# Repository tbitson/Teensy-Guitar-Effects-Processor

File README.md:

Teensy Guitar Effects Processor

This is an in-work project!

The Teensy Guitar Effects Processor (Teensy GEP or just GEP) is a microcontroller based sound effects processor designed for enhancing and modifying electric guitar sounds. It uses a Teensy microcontroller paired with a dedicated sound processing chip to provide a multitude of effects. 

The base design uses a Teensy 3.2 along with the Teensy Audio Shield from PJRC (pjrc.com) to process stereo audio at a full 16-bit 44.1kHz sample rate. The audio shield supports line-level-in, line-level out, and has an on-board headphone jack. The shield also contain a micro-SD card slot to allow recording and playback of sound. A separate battery powered pre-amp module interfaces most common electric guitar pickups to the line-level input. 

The design inspiration for the Teensy GEP is based on a project that appeared in the July 2017 edition of Circuit Cellar magazine by Brian Miller.  The original version of the source code (dubbed 1.0) does not seem to have any significant change since the article was published, and no longer compiles with the current version of the Teensy compiler and/or audio libraries. Significant changes to the baseline code were required to a) bring up-to-date with current library versions, 2) match the current compiler versions, and 3) to simplify the code so that my limited brain power could understand how the code worked (or at least how I thought I worked). 

Starting with Version 1.4, the memory requirements exceeded the Teensy 3.2, and either a Teensy 3.5 or 3.6 must be used. The devices are pin-for-pin compatable, however the 3.5 and 3.6 are both physically long with additional pins. A re-spin of the PC board will include the new footprint. This project is NOT electrically compatible with Teensy 4.0, but the software is. Change the #define in hardware.h to select your device.

The next milestone is to create a class hierarchy for the effects to allow easy implementation of new effects and/or changes to existing effects.

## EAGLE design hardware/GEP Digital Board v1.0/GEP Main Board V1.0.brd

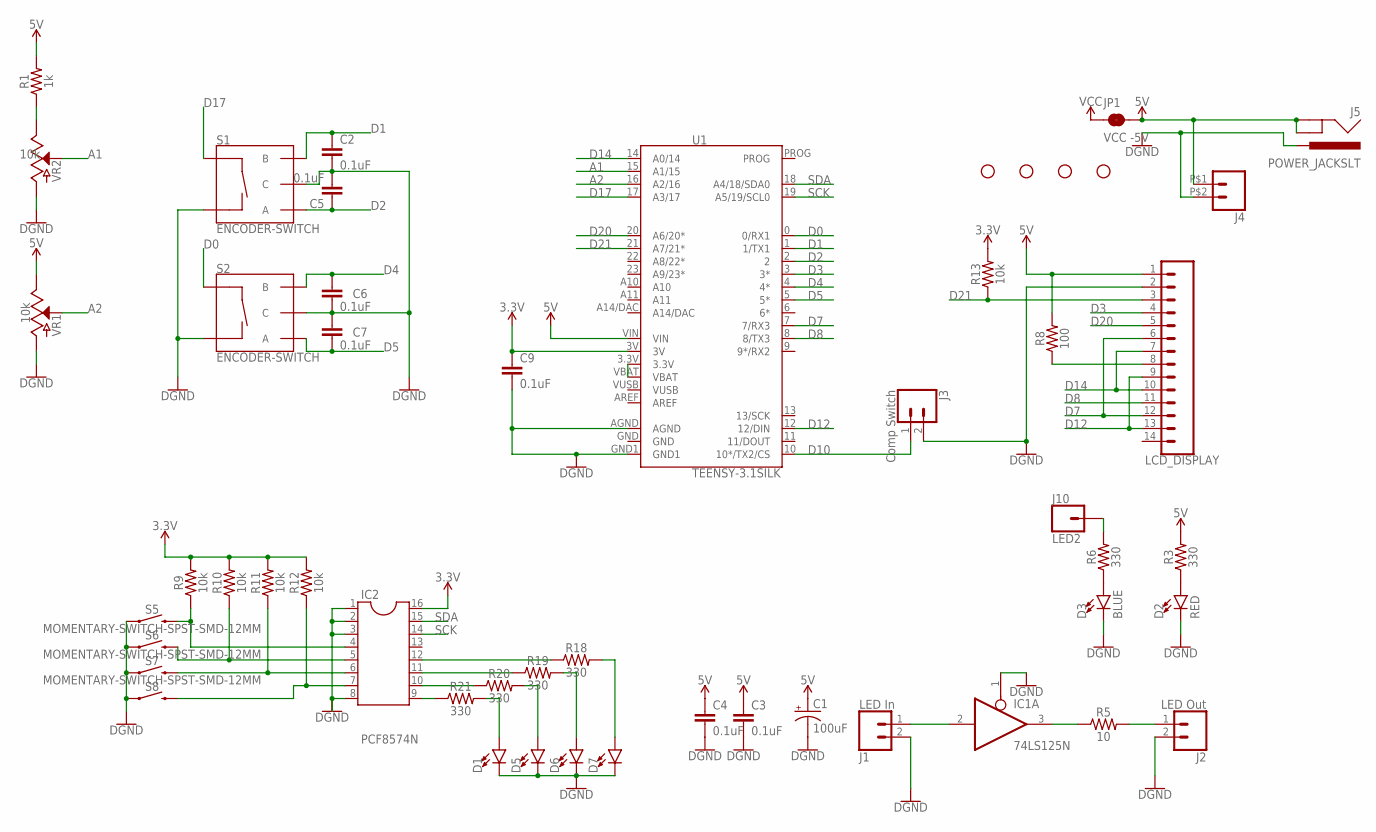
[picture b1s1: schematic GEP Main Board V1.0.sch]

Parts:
C1: 100uF; CPOL-RADIAL-2.5MM-6.5MM
C2, C3, C4, C5, C6, C7, C9: 0.1uF; CAP-PTH-SMALL-KIT
D1, D5, D6, D7: LED5MM; LED_5MM
D2: RED; LED_5MM
D3: BLUE; LED_5MM
H1, H2, H3, H4: STAND-OFF
IC1: 74LS125N; DIL14
IC2: PCF8574N; SOCKET-16
J1: LED In; 1X02
J2: LED Out; 1X02
J3: Comp Switch; 1X02
J4: CONN_02PTH2; 1X02_BIG
J5: POWER_JACKSLT; POWER_JACK_SLOT
J10: LED2; 1X01
JP1: VCC -5V; SMT-JUMPER_2_NC_TRACE_SILK
LCDDISPLAY: LCD_DISPLAY; 1X14
R1: 1k; AXIAL-0.3
R3, R6, R18, R19, R20, R21: 330; AXIAL-0.3
R5: 10; AXIAL-0.3
R8: 100; AXIAL-0.3
R9, R10, R11, R12, R13: 10k; AXIAL-0.3
S1, S2: ENCODER-SWITCH; ROTARY_ENC_PLAIN
S5, S6, S7, S8: MOMENTARY-SWITCH-SPST-SMD-12MM; TACTILE_SWITCH_SMD_12MM
U1: TEENSY-3.1SILK; TEENSY-3.1
VR1, VR2: 10k; POT-PTH-ALPS-KIT

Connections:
3.3V: C9.1, IC2.16, R9.P$2 (2), R10.P$2 (2), R11.P$2 (2), R12.P$2 (2), R13.P$2 (2), U1.3V
5V: C1.1 (+), C3.1, C4.1, J4.P$1 (1), J5.GND@1 (GNDBREAK), J5.GND@2 (GND), JP1.2, LCDDISPLAY.1, R1.P$2 (2), R3.P$2 (2), R8.P$2 (2), U1.VIN, VR1.P$1 (E)
A1: U1.15 (A1/15), VR2.P$2 (S)
A2: U1.16 (A2/16), VR1.P$2 (S)
D0: S2.SW+, U1.0 (0/RX1)
D1: C2.1, S1.B, U1.1 (1/TX1)
D2: C5.1, S1.A, U1.2
D3: LCDDISPLAY.4, U1.3 (3*)
D4: C6.1, S2.B, U1.4 (4*)
D5: C7.2, S2.A, U1.5 (5*)
D7: LCDDISPLAY.6, LCDDISPLAY.12, U1.7 (7/RX3)
D8: LCDDISPLAY.11, U1.8 (8/TX3)
D10: J3.1, U1.10 (10*/TX2/CS)
D12: LCDDISPLAY.9, LCDDISPLAY.13, U1.12 (12/DIN)
D14: LCDDISPLAY.7, LCDDISPLAY.10, U1.14 (A0/14)
D17: S1.SW+, U1.17 (A3/17)
D20: LCDDISPLAY.5, U1.20 (A6/20*)
D21: LCDDISPLAY.3, R13.P$1 (1), U1.21 (A7/21*)
GND: C1.2 (-), C2.2, C3.2, C4.2, C5.2, C6.2, C7.1, C9.2, D1.K (C), D2.K (C), D3.K (C), D5.K (C), D6.K (C), D7.K (C), IC1.1 (OE), IC1.7 (GND), IC2.1, IC2.2, IC2.3, IC2.8, J1.2, J2.2, J3.2, J4.P$2 (2), J5.PWR, LCDDISPLAY.2, S1.C, S1.SW-, S2.C, S2.SW-, S5.1, S6.1, S7.1, S8.1, U1.AGND, U1.GND, U1.GND1, VR1.P$3 (A), VR2.P$3 (A)
LED: LCDDISPLAY.8, R8.P$1 (1)
unnamed: U1.3.3V, U1.VBAT
unnamed: IC2.9, R21.P$1 (1)
unnamed: IC2.10, R20.P$1 (1)
unnamed: IC1.2 (I), J1.1
unnamed: IC1.3 (O), R5.P$1 (1)
unnamed: R1.P$1 (1), VR2.P$1 (E)
unnamed: D3.A, R6.P$1 (1)
unnamed: D2.A, R3.P$1 (1)
unnamed: IC2.5, R10.P$1 (1), S6.3 (2)
unnamed: IC2.6, R11.P$1 (1), S7.3 (2)
unnamed: IC2.7, R12.P$1 (1), S8.3 (2)
unnamed: IC2.4, R9.P$1 (1), S5.3 (2)
unnamed: J2.1, R5.P$2 (2)
unnamed: IC2.11, R19.P$1 (1)
unnamed: IC2.12, R18.P$1 (1)
unnamed: D1.A, R21.P$2 (2)
unnamed: D5.A, R20.P$2 (2)
unnamed: D6.A, R19.P$2 (2)
unnamed: D7.A, R18.P$2 (2)
unnamed: J10.1, R6.P$2 (2)
SCK: IC2.14, U1.19 (A5/19/SCL0)
SDA: IC2.15, U1.18 (A4/18/SDA0)
VCC: IC1.14 (VCC), JP1.1
VUSB: U1.VUSB

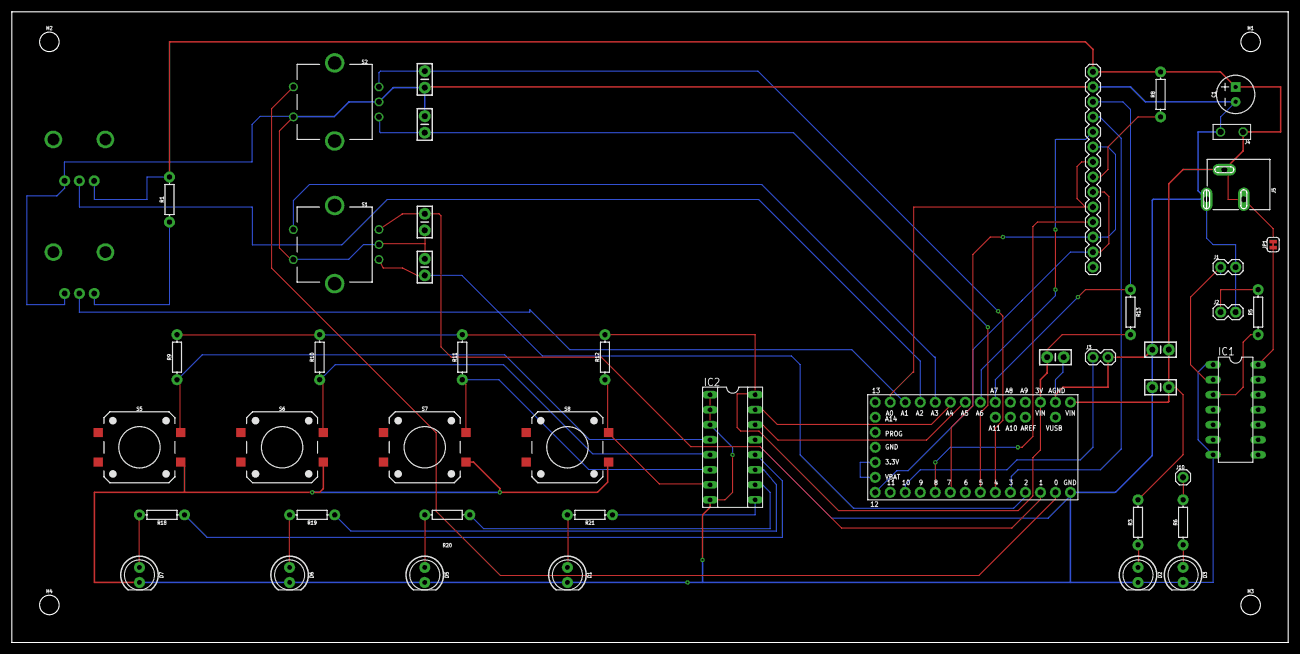
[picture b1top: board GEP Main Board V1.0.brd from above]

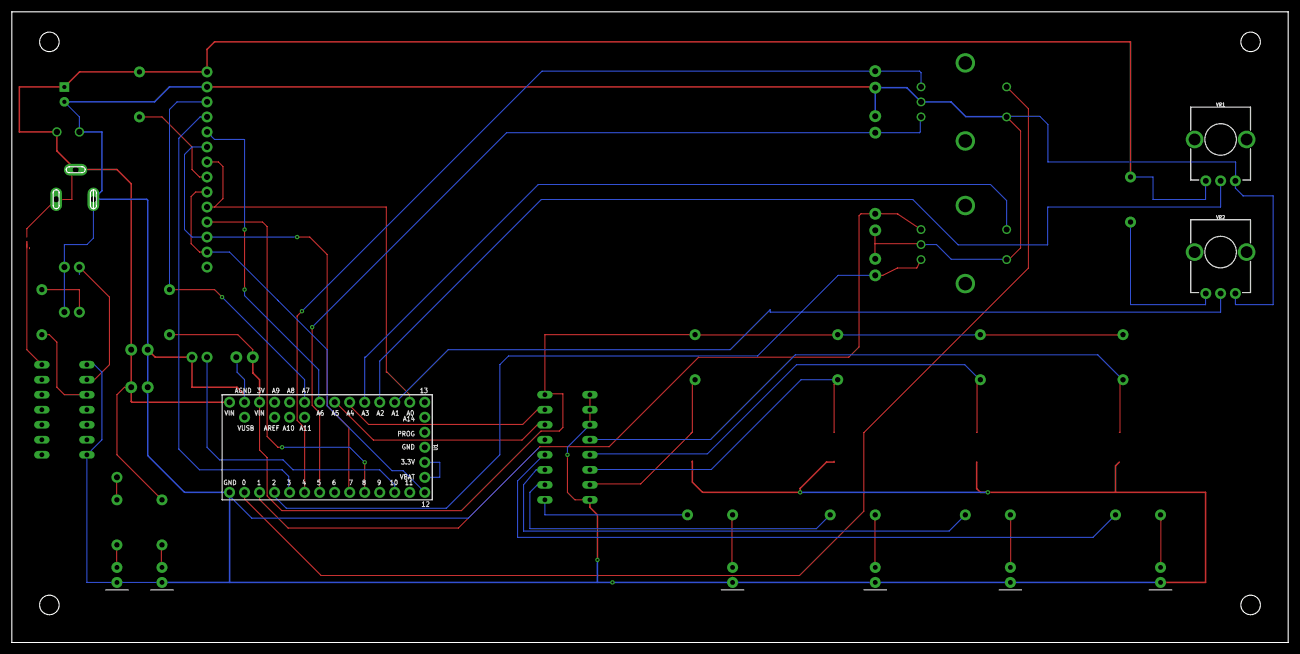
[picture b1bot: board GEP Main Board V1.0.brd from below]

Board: 2 copper layers, 215.9 x 106.7 mm, 51 parts (3 on the bottom side), 43 nets.

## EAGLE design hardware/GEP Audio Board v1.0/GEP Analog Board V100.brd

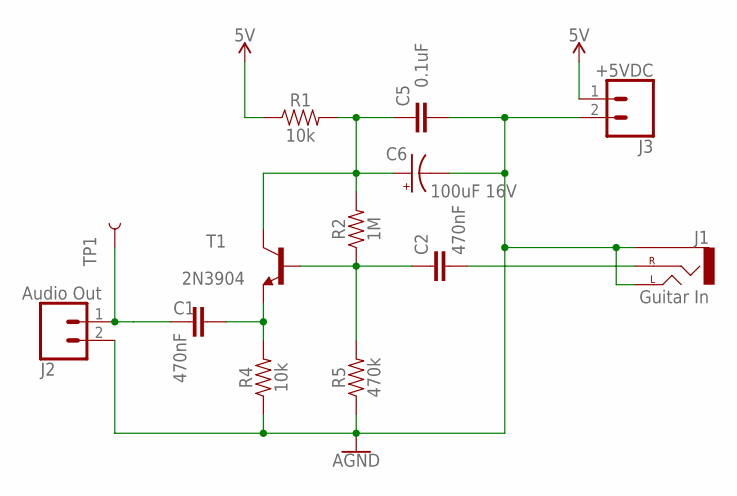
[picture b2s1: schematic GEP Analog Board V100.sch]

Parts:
C1, C2: 470nF; CAP-PTH-SMALL-KIT
C5: 0.1uF; CAP-PTH-SMALL-KIT
C6: 100uF 16V; CPOL-RADIAL-2.5MM-6.5MM
J1: Guitar In; STEREOJACK2.5MM_SPECIAL_POGOPINS
J2: Audio Out; 1X02
J3: +5VDC; 1X02
R1, R4: 10k; AXIAL-0.3
R2: 1M; AXIAL-0.3
R5: 470k; AXIAL-0.3
T1: 2N3904; TO92
TP1: TEST-POINTTP_15TH_THRU; TP_15TH

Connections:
5V: J3.1, R1.P$1 (1)
AGND: C5.2, C6.2 (-), J1.RING1 (SLEEVE), J1.SHIELD (LEFT), J2.2, J3.2, R4.P$1 (1), R5.P$1 (1)
unnamed: C2.1, R2.P$1 (1), R5.P$2 (2), T1.2 (B)
unnamed: C2.2, J1.TIP (RIGHT)
unnamed: C1.2, J2.1, TP1.P$1
unnamed: C1.1, R4.P$2 (2), T1.3 (E)
unnamed: C5.1, C6.1 (+), R1.P$2 (2), R2.P$2 (2), T1.1 (C)

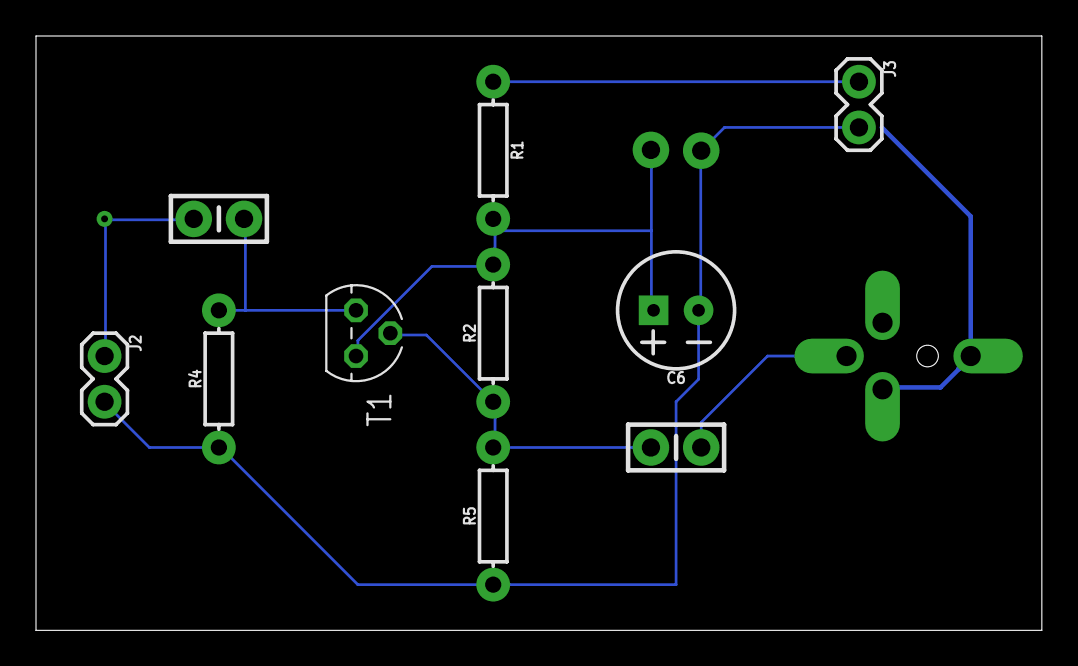
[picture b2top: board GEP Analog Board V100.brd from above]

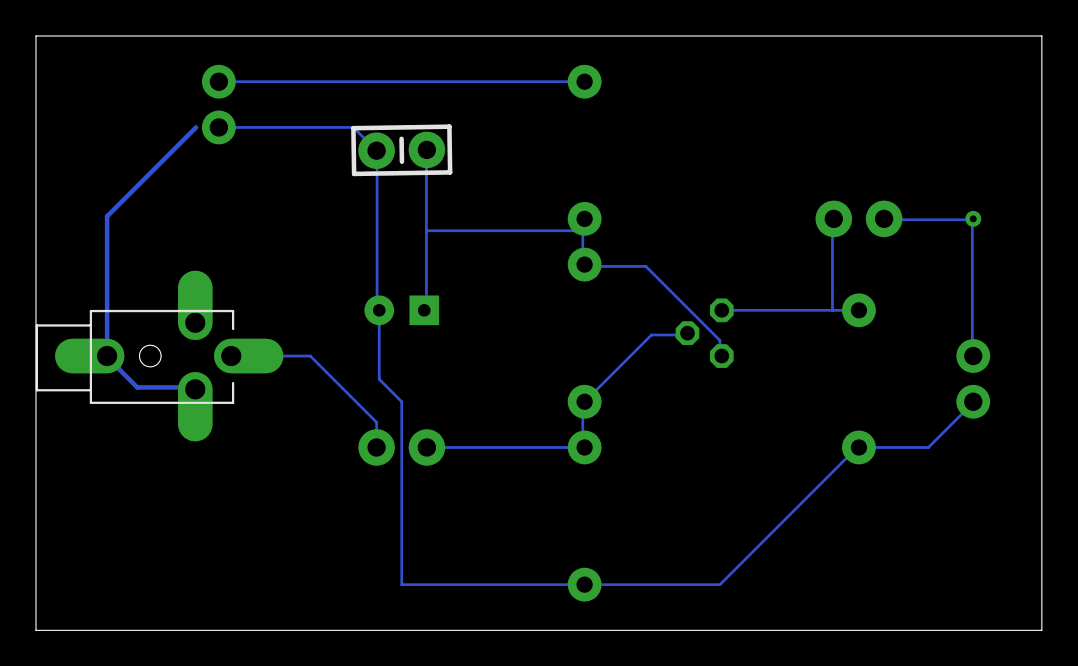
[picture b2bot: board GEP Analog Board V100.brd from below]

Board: 2 copper layers, 55.9 x 33.0 mm, 13 parts (2 on the bottom side), 7 nets.

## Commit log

2020-01-15 Complete organization change, some gui code rewritten, added multi-delay effect and screen
2020-01-15 Rewrite Continuing, preparing for "classification" of effects
2020-01-15 Major cleanup, bug fixes
    Holding down tuner button sets a dev mode that allows changes to behavior without affecting normal operation. Use to enable test tone using wahwah button. Enabled headphones output in addion to line 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
2020-01-17 Delete .DS_Store
    Mac OS file unneeded
2022-07-25 Update to 1.68
    Minor cleanup
2022-07-25 Added hardware files
    General cleanup
2022-07-25 General cleanup
    Sync to version 1.8.5
2022-07-25 Sync to 1.8.5
2022-07-25 Sync Master to 1.8.5
    Update to 1.8.5
2022-07-25 Sync to master

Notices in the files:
parts and their libraries:
SparkFun-Capacitors: Licensing: Creative Commons ShareAlike 4.0 International - https://creativecommons.org/licenses/by-sa/4.0
